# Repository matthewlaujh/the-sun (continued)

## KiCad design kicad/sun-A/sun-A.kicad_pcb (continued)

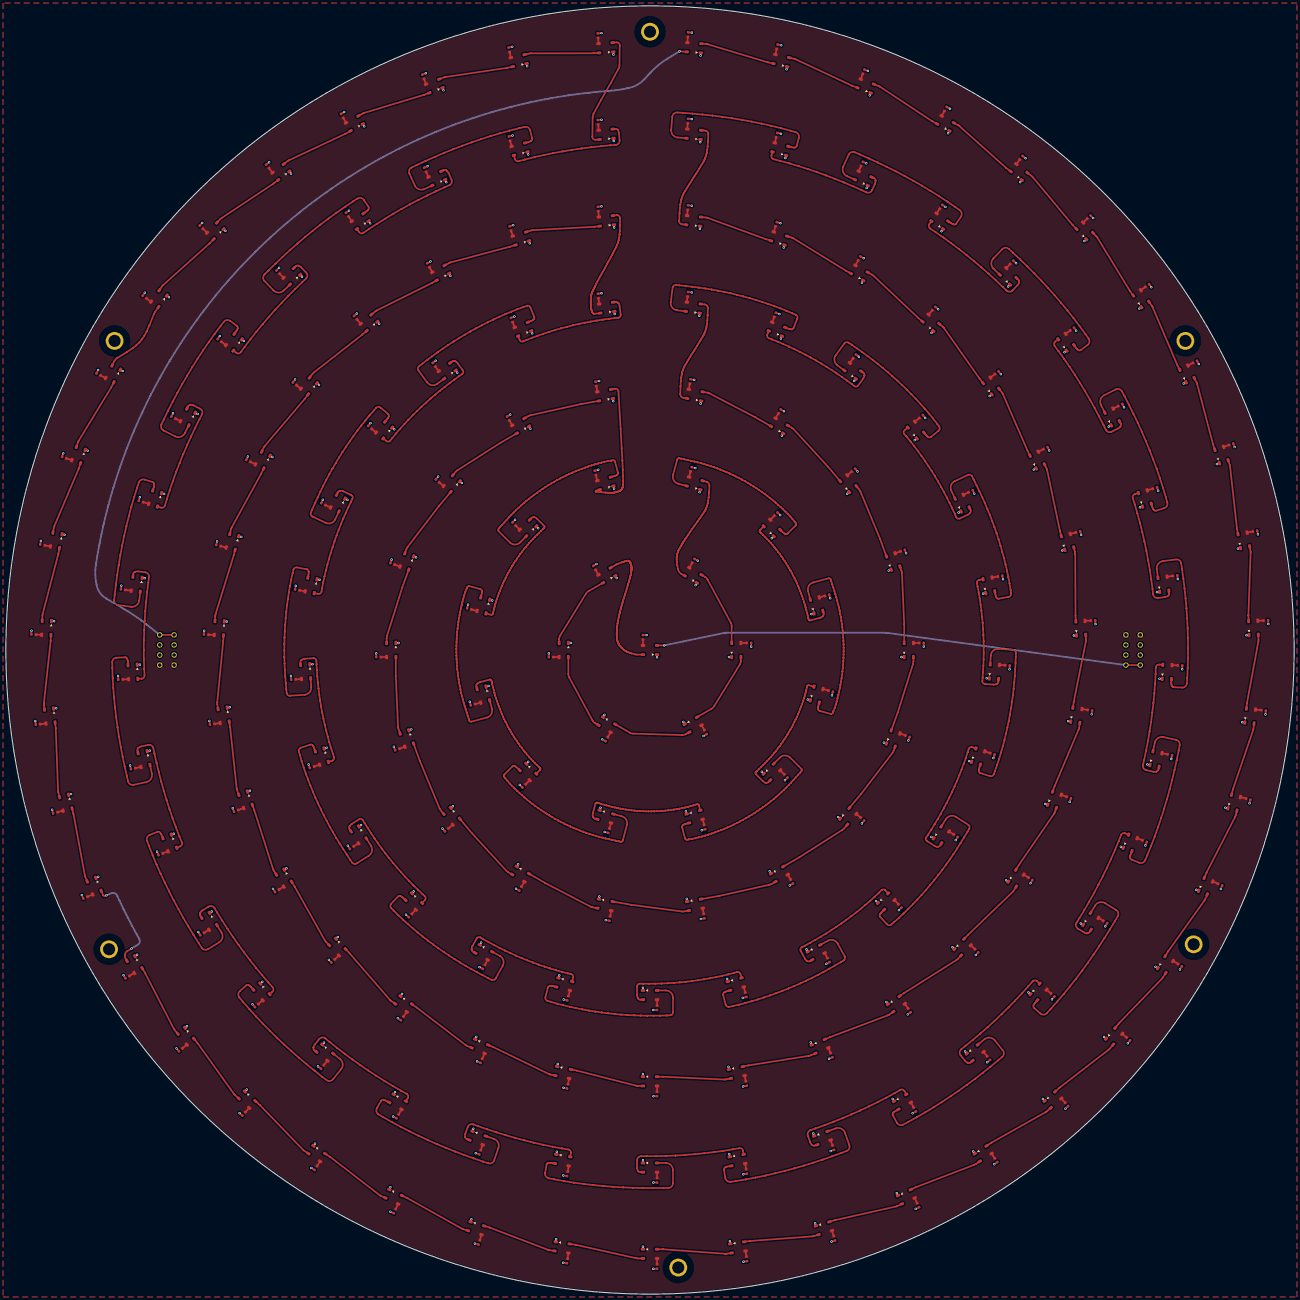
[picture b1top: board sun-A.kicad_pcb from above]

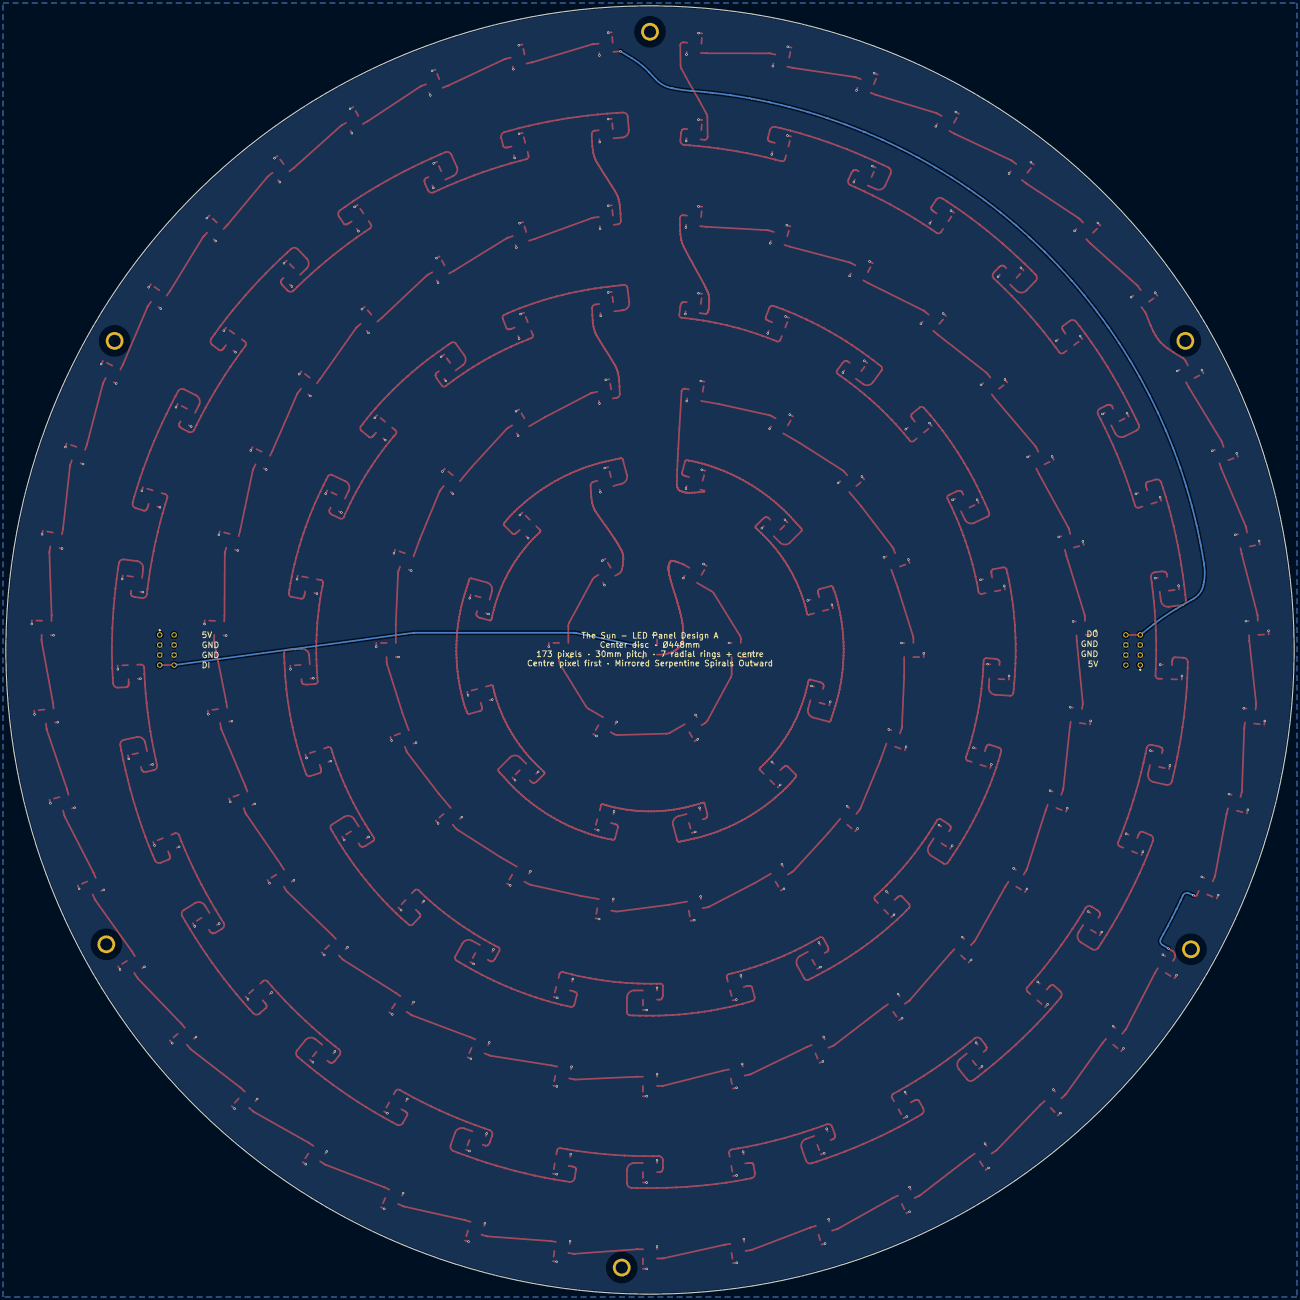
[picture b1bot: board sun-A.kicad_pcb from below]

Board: 2 copper layers, 448.0 x 448.0 mm, 354 parts (8 on the bottom side), 176 nets.

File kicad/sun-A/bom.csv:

Comment,Designator,Footprint,LCSC Part #
SKC6812RGBW-NW (white face),"LED1,LED2,LED3,LED4,LED5,LED6,LED7,LED8,LED9,LED10,LED11,LED12,LED13,LED14,LED15,LED16,LED17,LED18,LED19,LED20,LED21,LED22,LED23,LED24,LED25,LED26,LED27,LED28,LED29,LED30,LED31,LED32,LED33,LED34,LED35,LED36,LED37,LED38,LED39,LED40,LED41,LED42,LED43,LED44,LED45,LED46,LED47,LED48,LED49,LED50,LED51,LED52,LED53,LED54,LED55,LED56,LED57,LED58,LED59,LED60,LED61,LED62,LED63,LED64,LED65,LED66,LED67,LED68,LED69,LED70,LED71,LED72,LED73,LED74,LED75,LED76,LED77,LED78,LED79,LED80,LED81,LED82,LED83,LED84,LED85,LED86,LED87,LED88,LED89,LED90,LED91,LED92,LED93,LED94,LED95,LED96,LED97,LED98,LED99,LED100,LED101,LED102,LED103,LED104,LED105,LED106,LED107,LED108,LED109,LED110,LED111,LED112,LED113,LED114,LED115,LED116,LED117,LED118,LED119,LED120,LED121,LED122,LED123,LED124,LED125,LED126,LED127,LED128,LED129,LED130,LED131,LED132,LED133,LED134,LED135,LED136,LED137,LED138,LED139,LED140,LED141,LED142,LED143,LED144,LED145,LED146,LED147,LED148,LED149,LED150,LED151,LED152,LED153,LED154,LED155,LED156,LED157,LED158,LED159,LED160,LED161,LED162,LED163,LED164,LED165,LED166,LED167,LED168,LED169,LED170,LED171,LED172,LED173",LED_SKC6812RGBW_5050,C5348912
100nF 50V X7R,"C1,C2,C3,C4,C5,C6,C7,C8,C9,C10,C11,C12,C13,C14,C15,C16,C17,C18,C19,C20,C21,C22,C23,C24,C25,C26,C27,C28,C29,C30,C31,C32,C33,C34,C35,C36,C37,C38,C39,C40,C41,C42,C43,C44,C45,C46,C47,C48,C49,C50,C51,C52,C53,C54,C55,C56,C57,C58,C59,C60,C61,C62,C63,C64,C65,C66,C67,C68,C69,C70,C71,C72,C73,C74,C75,C76,C77,C78,C79,C80,C81,C82,C83,C84,C85,C86,C87,C88,C89,C90,C91,C92,C93,C94,C95,C96,C97,C98,C99,C100,C101,C102,C103,C104,C105,C106,C107,C108,C109,C110,C111,C112,C113,C114,C115,C116,C117,C118,C119,C120,C121,C122,C123,C124,C125,C126,C127,C128,C129,C130,C131,C132,C133,C134,C135,C136,C137,C138,C139,C140,C141,C142,C143,C144,C145,C146,C147,C148,C149,C150,C151,C152,C153,C154,C155,C156,C157,C158,C159,C160,C161,C162,C163,C164,C165,C166,C167,C168,C169,C170,C171,C172,C173",C_0603_1608Metric,C1591
M3x30 SMT standoff BZXC BSMTSO family - CONFIRM 30mm P/N (stocked C20617225 is 3mm),"MH1,MH2,MH3,MH4,MH5,MH6",MH_M3_SMT_Standoff_BZXC,C20617225
"WAGO 2601-3104 (hand solder from BACK side, not JLC; poles 5V/GND/GND/DATA)","J_IN,J_OUT",WAGO_2601-3104_THT,
